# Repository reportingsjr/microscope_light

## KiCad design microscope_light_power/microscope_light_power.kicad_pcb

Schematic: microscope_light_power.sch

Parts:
BT1: Battery connector; JST_PH_S2B-PH-K_02x2.00mm_Angled
C1, C4, C5, C6, C7: 10uF; C_0805_HandSoldering
C2: 0.1uF; C_0603_HandSoldering
C3: 100uF; CP_Radial_D8.0mm_P3.50mm
D1: charging; LED_0603_HandSoldering
D2: done; LED_0603_HandSoldering
J1: MICROUSB; MICROUSB_MOLEX_47589-0001; Farnell 1568023
J2: 5V175_out; JST_PH_S2B-PH-K_02x2.00mm_Angled
J3: enable_switch; JST_PH_S2B-PH-K_02x2.00mm_Angled
L1: 10uH; Inductor_Taiyo-Yuden_NR-80xx_HandSoldering; part number NR8040T100M
MK1, MK2, MK3, MK4: Mounting_Hole; MountingHole_3.2mm_M3_ISO14580
R1: 2.15M; R_0603_HandSoldering; part number RC0603FR-072M15L
R2: 430k; R_0603_HandSoldering
R4: 270k; R_0603_HandSoldering
R5: 100k; R_0603_HandSoldering
R6, R10, R11: 1k; R_0603_HandSoldering
R7: 20k; R_0603_HandSoldering
R8: 1.87M; R_0603_HandSoldering; part number RC0603FR-071M87L
R9: 200k; R_0603_HandSoldering
ROff3: 200k; R_0603_HandSoldering
ROn3: 200k; R_0603_HandSoldering
TH1: 10k; JST_PH_S2B-PH-K_02x2.00mm_Angled
TP1, TP2, TP3, TP4: TESTPAD; Measurement_Point_Round-TH_Big
U1: MCP73871-2AA; QFN-20-1EP_4x4mm_Pitch0.5mm
U2: TPS61090; QFN-16-1EP_4x4mm_Pitch0.65mm

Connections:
/5V175: C3.1, C4.1, J2.1, R8.1, TP2.1, U2.1, U2.15, U2.16
/SW: L1.2, U2.3, U2.4
/Vbat: BT1.1, C6.1, TP3.1, U1.14 (VBAT), U1.15 (VBAT), U1.16 (Vbat_SENSE)
/Vout: C2.1, C5.1, C7.1, L1.1, R1.1, ROn3.1, TP4.1, U1.1 (OUT), U1.20 (OUT), U2.8, U2.10
/Vusb: C1.1, D1.2, D2.2, J1.1, R4.2, TP1.1, U1.3 (SEL), U1.4 (PROG2), U1.9 (~TE), U1.17 (CE), U1.18 (IN), U1.19 (IN)
/enable: J3.2, ROff3.1, ROn3.2, U2.11
/low_battery: U2.12; also elsewhere on the board
GND: BT1.2, C1.2, C2.2, C3.2, C4.2, C5.2, C6.2, C7.2, J1.5, J1.S, J2.2, J3.1, R2.2, R5.2, R6.2, R7.2, R9.2, ROff3.2, TH1.2, U1.10 (VSS), U1.11 (VSS), U1.21 (VSS), U2.5, U2.6, U2.7, U2.13, U2.17; also elsewhere on the board
unnamed: D1.1, R10.1
unnamed: D2.1, R11.1
unnamed: R1.2, R2.1, U2.9
unnamed: R4.1, R5.1, U1.2 (VPCC)
unnamed: R6.1, U1.13 (PROG1)
unnamed: R7.1, U1.12 (PROG3)
unnamed: R8.2, R9.1, U2.14
unnamed: R10.2, U1.8 (STAT1/~LBO~)
unnamed: R11.2, U1.7 (STAT2)
unnamed: TH1.1, U1.5 (THERM)

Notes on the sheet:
System limits charging current once Vusb has sagged to 4.55V as set by this voltage divider.
Charge current is 1A set by PROG1.
Charge termination current is 50mA as set by PROG3.
The thermistor has a bizarre PCB trace because I didn't want to break up the ground plane. By the time I realized this a good chunk of the board was already laid out.
Populate ROn3 to have the output on normally. Populate ROff3 to have the output off normally.

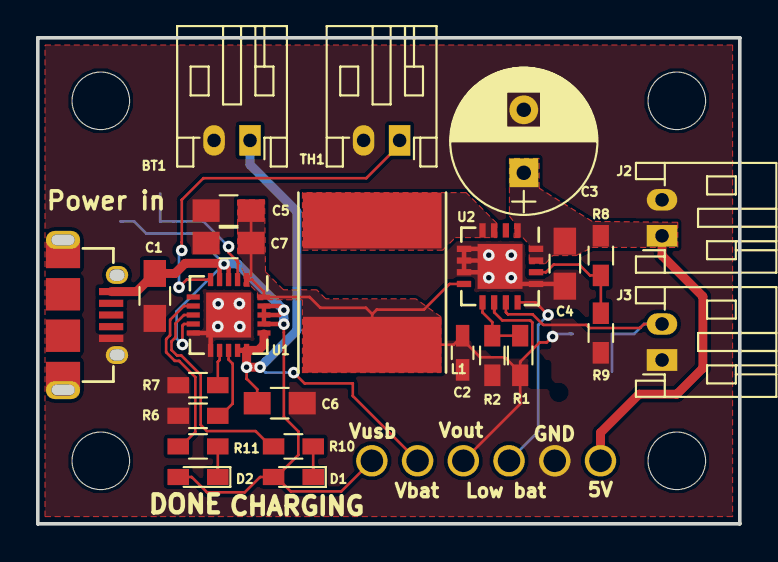
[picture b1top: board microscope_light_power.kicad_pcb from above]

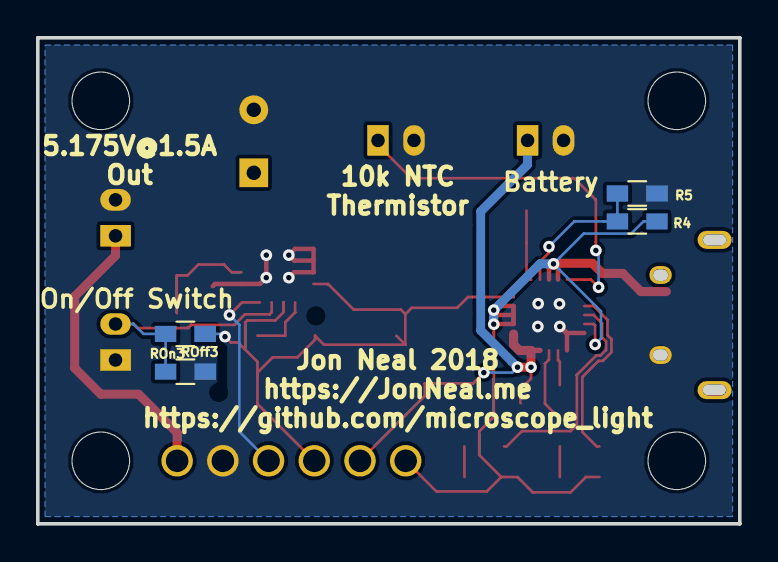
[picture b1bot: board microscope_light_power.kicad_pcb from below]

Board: 2 copper layers, 38.5 x 26.6 mm, 39 parts (4 on the bottom side), 18 nets.

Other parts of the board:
TP2#2, TP2#3: TESTPAD; Measurement_Point_Round-TH_Big

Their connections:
/low_battery: TP2#3.1; also elsewhere on the board
GND: TP2#2.1; also elsewhere on the board

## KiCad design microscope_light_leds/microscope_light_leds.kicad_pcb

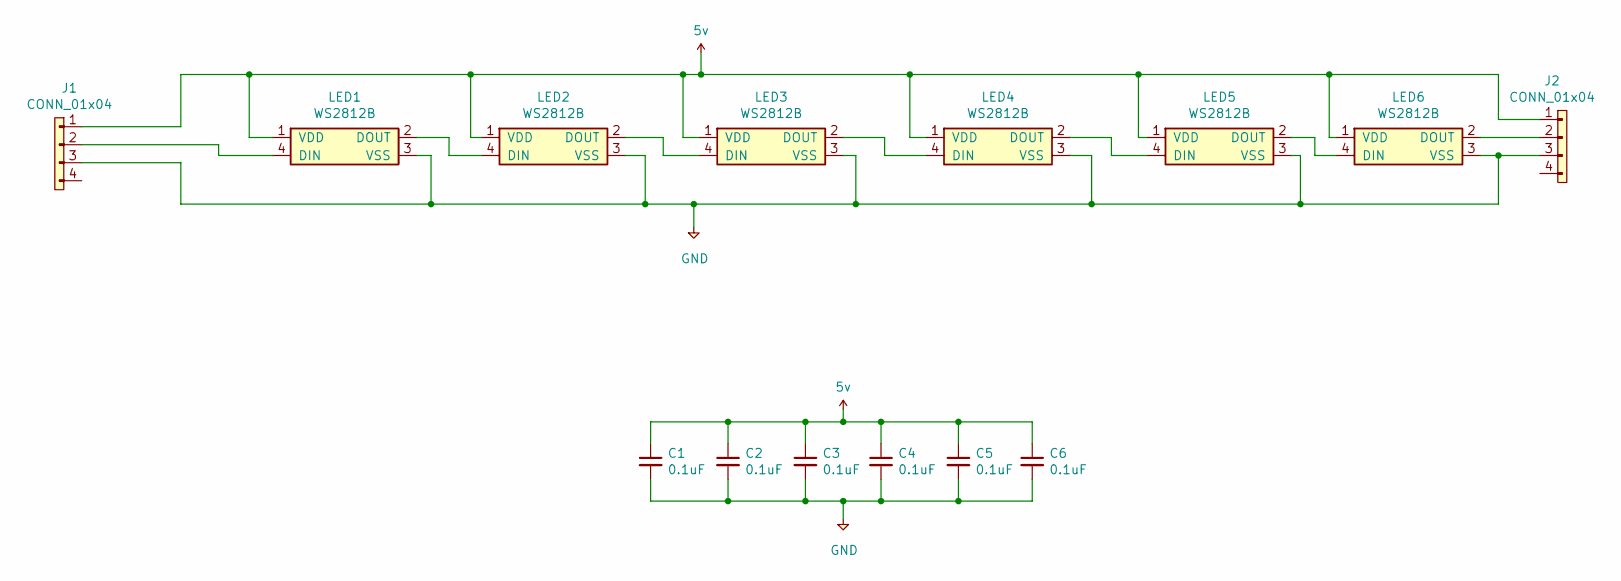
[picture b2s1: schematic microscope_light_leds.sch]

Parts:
C1, C2, C3, C4, C5, C6: 0.1uF; C_0603_HandSoldering
J1, J2: CONN_01x04; JST_PH_B4B-PH-K_04x2.00mm_Straight
LED1, LED2, LED3, LED4, LED5, LED6: WS2812B; LED_WS2812B-PLCC4

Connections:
5v: C1.1, C2.1, C3.1, C4.1, C5.1, C6.1, J1.1, J2.1, LED1.1 (VDD), LED2.1 (VDD), LED3.1 (VDD), LED4.1 (VDD), LED5.1 (VDD), LED6.1 (VDD)
GND: C1.2, C2.2, C3.2, C4.2, C5.2, C6.2, J1.3, J2.3, LED1.3 (VSS), LED2.3 (VSS), LED3.3 (VSS), LED4.3 (VSS), LED5.3 (VSS), LED6.3 (VSS)
unnamed: J1.2, LED1.4 (DIN)
unnamed: J2.2, LED6.2 (DOUT)
unnamed: LED1.2 (DOUT), LED2.4 (DIN)
unnamed: LED2.2 (DOUT), LED3.4 (DIN)
unnamed: LED3.2 (DOUT), LED4.4 (DIN)
unnamed: LED4.2 (DOUT), LED5.4 (DIN)
unnamed: LED5.2 (DOUT), LED6.4 (DIN)

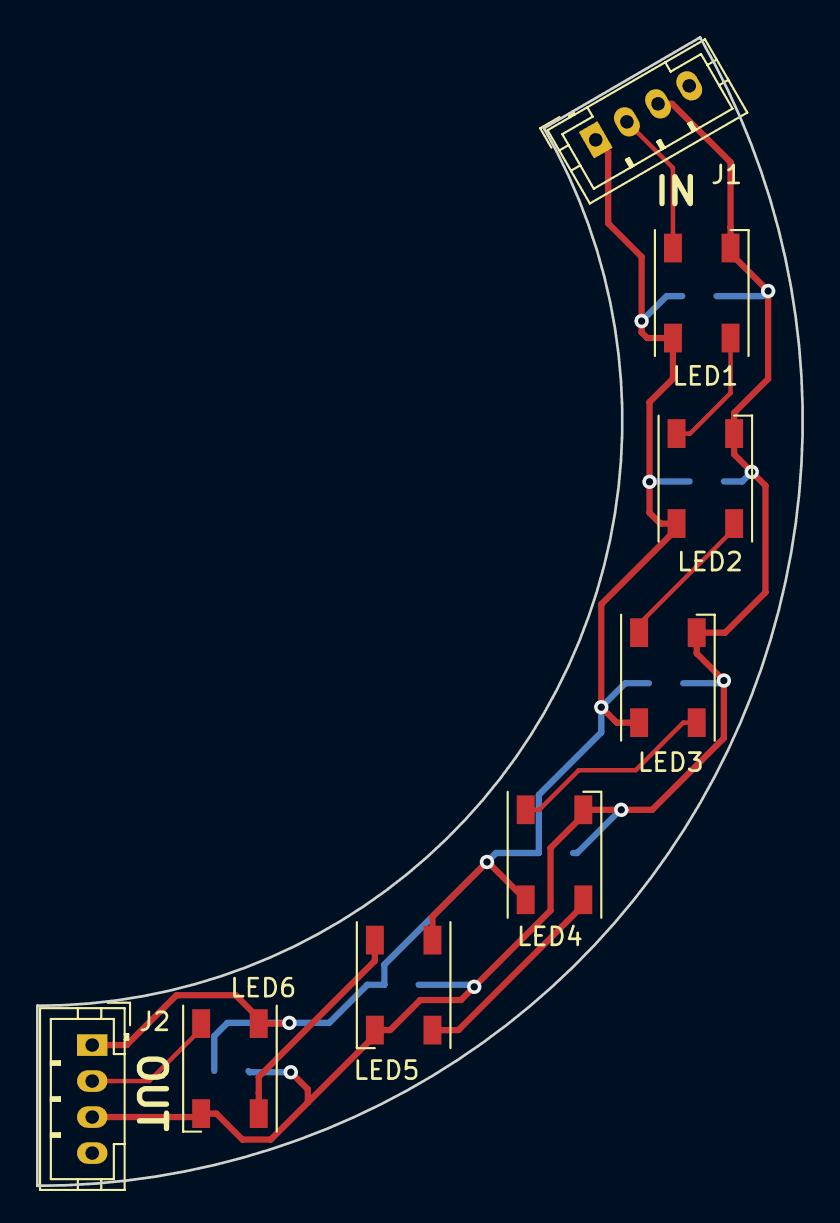
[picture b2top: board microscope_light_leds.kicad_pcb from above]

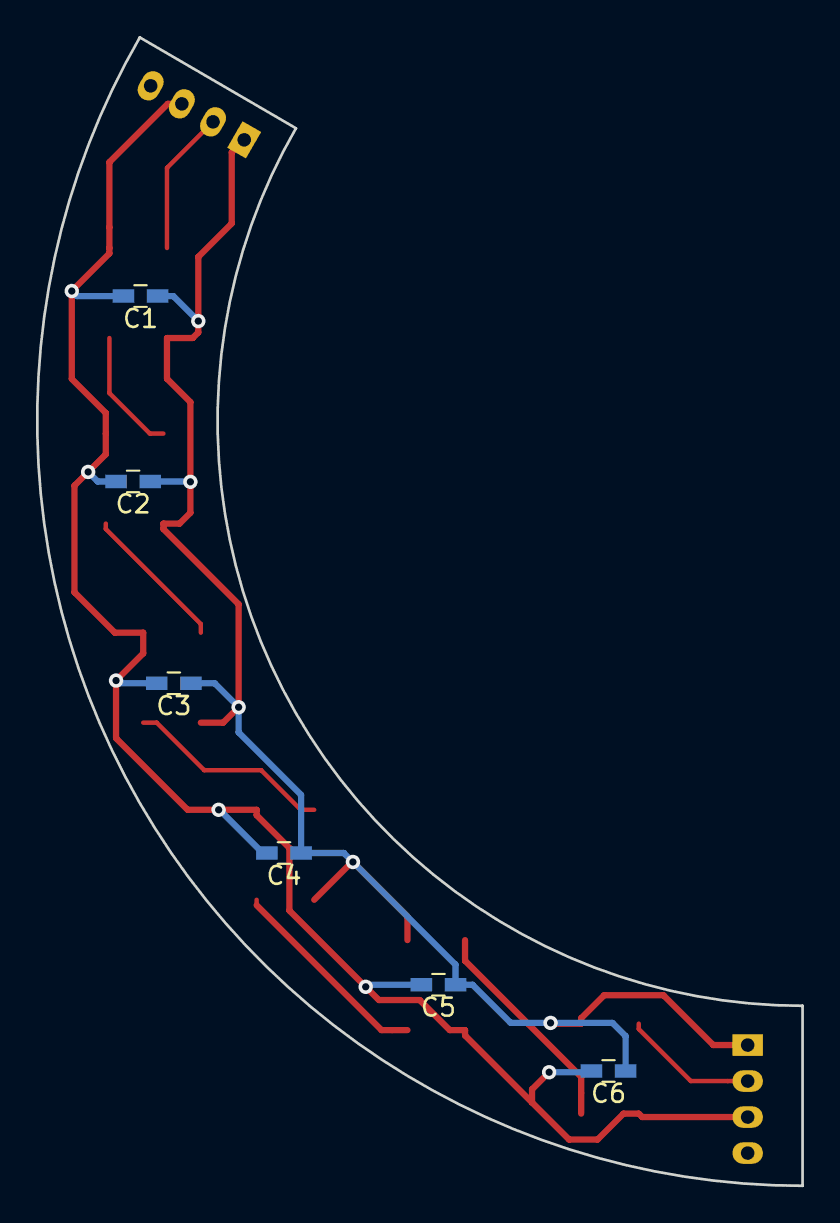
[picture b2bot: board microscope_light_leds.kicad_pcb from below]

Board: 2 copper layers, 42.5 x 63.8 mm, 14 parts (6 on the bottom side), 9 nets.

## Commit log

2017-10-08 Added agg-kicad library and set up a kicad project for the power board. So far the battery charge controller/load manager has been drawn in the schematic.
2017-10-08 Add some bypass capacitance to the battery management unit power output.
2017-10-09 Drew schematic for the boost converter. Last bit is connectors and small detail work.
2017-10-09 Added M3 mounting holes in schematic.
2017-10-09 Added power out connector and enable switch connector. A handful of test points were also added (I finally remembered to do this before sending a board out!!!!)
2017-10-10 Update agg-kicad library.
2017-10-10 Select footprint for the last part (10uH inductor). Ready to move on to laying out the PCB!
2017-10-10 Imported parts in to the PCB.
2017-10-10 Added a 40mm x 70mm board layout.
2017-10-11 Arranged the components in a slightly more organized manner. This is mainly just to see how much room there is to work with and to get an idea of how the components should flow. Also added a gitignor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
2017-10-12 Put the parts for the MCP73871 battery charger in better locations. Some labeling was also placed to make sure the board can be used without looking at the schematic every time!
2017-10-12 After getting most things organized I saw that we can do better! Reduced the board length from 70mm to 50mm and started rearranging components to fit.
2017-10-12 Getting closer to a reasonable arrangement of components.
2017-10-14 Route the most critical power traces.
2017-10-14 Route some more high current traces.
2017-10-14 Routed all of the direct connections from the MCP73871. I also added a note about the very bizarre routing for the thermistor. By the time I realized its trace would have to go on the bottom a good c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
2017-10-14 Routed everything connected to the TPS61090. Also routed the test points and connectors. Only thing left is ground!
2017-10-15 Change the TPS61090 annotation from IC* to U* and move the reference designator on to the silkscreen layer.
2017-10-15 Added edge.cuts lines on top of the microusb connector slots since oshpark doesn't support gerber slot callouts.
2017-10-15 Add more silkscreen labels for clarity
2017-10-15 Added OSHW symbol
2017-11-16 Add datasheets for ICs used.
2017-11-16 Update gitignore to ignore more backup files
2017-11-16 Updated TPS61090 footprint to the correct footprint and modified the symbol to match KLC. sym-lib-table is due to a recent change in KiCad.
2017-11-16 The symbol library table update barfed and forgot which libraries all of my parts were in. I went through and manually added them back in.
2017-11-17 Continue unfucking library stuff after the symbol table update. Grumble grumble.
2017-11-17 Added LED board project with a layout that might be tweaked a bit. I am going to sit on it and think for a bit. Removed .bak files from gitignore (it is a fairly helpful file, who knew?).
2017-12-02 Finish first (and hopefully last) design of the LED ring.
2017-12-03 Rust firmware that so far blinks one of the LEDs on the STM32F4 disco board.
2018-05-17 Remove rust firmware in favor of C/libopencm3 firmware for right now.
2018-05-17 Add C generated files to gitignore
2018-05-17 Add some mediocre C/libopencm3 firmware.
2018-05-18 Add .elf files to the .gitignore
2018-05-18 Remove .elf file from git
2018-05-18 Firmware now compiles. First verison of moving average implemented. Untested on hardware.
2018-05-30 Start redoing the layout to fix some major and minor problems with this design: * The SMPS output filter caps are way too far away from the IC. This keeps killing the internal MOSFET which fails as a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
2018-05-30 Add resistors to select normally on/normally off output. Scrunch in more components, shift things around a bit, etc etc.
2018-05-31 Switch the thermistor footprint to another JST PH connector. Smash everything closer together. Adjusted the test pad footprints.
2018-05-31 Route the MCP73871
2018-05-31 Route TPS61090. Need to add vias and do final adjustment.
